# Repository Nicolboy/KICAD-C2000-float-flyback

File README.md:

# KICAD-C2000-float-flyback

- **18.9W** — real-world target power, simulated efficiency up to 92.1%
- **+4.6 to +10.7 points** efficiency from synchronous rectification (UCC24612) vs. body-diode, depending on operating point
- **107.2V → 58.4–63.5V** — secondary overvoltage, resolved by a TVS clamp sized through simulation (×1.6 margin vs. the 100V MOSFET rating)
- PCB **routed 100% on 4 layers**, DRC clean

Flyback power supply for vacuum-tube filament heating and a low-noise
preamp stage, designed in KiCad 10, with the control side (C2000)
galvanically isolated from the power stage. **Update 2026-10-25**: the
secondary is no longer floating/galvanically isolated from the primary
in the final assembly — only the control↔power barrier remains isolated;
see `doc/plan-isolation-4couches.md` for the current barrier scope.
200kHz, 11–25V in → 5.5–13V/3A out, secondary liftable 0–90V for
cathode/filament stress reduction. Synchronous secondary rectification
(UCC24612, direct Vds sensing — no firmware timing) validated by SPICE at
the real 18.9W target, including a secondary-side overvoltage finding and
the clamp that fixes it — see *Validation* below for the figures and
`doc/sim-vs-mesure.md` for the full data.

Alimentation flyback pour le chauffage de filaments de chauffage de tubes à vide, conçue sous KiCad 10 — le côté
contrôle (C2000) reste isolé galvaniquement de l'étage de puissance.
**Mise à jour 2026-10-25** : le secondaire n'est plus flottant/isolé
galvaniquement du primaire dans le montage final — seule la barrière
contrôle↔puissance reste isolée ; voir `doc/plan-isolation-4couches.md`
pour le périmètre actuel des barrières.

Convertisseur flyback 200kHz, 11-25V en entrée → 5,5-13V/3A en sortie.
Secondaire élevable de 0 à 90V par un pont symétrique 2×100kΩ (une
résistance vers Vout+, une vers Vout-) — pour réduire le stress 
cathode/chauffage et le bruit de fond sur un préamplificateur à tubes bas bruit (montage cascode).

---

## Le point de conception le plus notable

Le redressement synchrone secondaire (Q2) est piloté par un **UCC24612**, pas
par le C2000 : ce contrôleur détecte directement le Vds de Q2 (diode
emulation) et pilote sa grille tout seul — aucun signal PWM ni isolateur
dédié à faire traverser la barrière pour ce canal. Avant ça, la commande
passait par un ISO7710+UCC27517 secondaires pilotés en PWM depuis le C2000 :
un timing fixé par le firmware, « à l'aveugle », sans retour sur le vrai Vds
de Q2 — remplacé une fois ce défaut identifié. L'UCC24612 est alimenté
directement depuis Vout (VDD dans sa plage 4,5-28V, pas de bootstrap
nécessaire) ; côté primaire, l'isolation PWM/EN (ISO7710 + UCC27517 + DPC817)
reste inchangée.

Chaque composant de puissance (MOSFETs, clamp, condensateurs d'entrée et de
sortie) est sourcé avec sa propre fiche datasheet dans `composants-datasheets/data/carte-flyback/`
(dépôt interne, non public — pas de lien)
— page citée, base (absolue / recommandée / typique / calculée), jamais de
valeur choisie à l'oeil. Ce sourcing a d'ailleurs fait revenir deux fois sur
le choix de Cin et Cout : le premier calcul prenait le cas 13V/3A (39W)
comme pire cas, avant d'être recorrigé sur les vrais cas d'usage — deux
câblages de filament qui tombent à **la même puissance réelle** (18,9W) et
divisent par deux la contrainte de courant et d'ondulation retenue au départ.
Le détail (formules, marges, historique des choix) est dans
[`00-intention-conception.md`](00-intention-conception.md).

---

## Architecture

| Bloc | Rôle |
|---|---|
| Primaire | Cin, Q1 (MOSFET N TO-252), clamp TVS D1 (boîtier SMC), U1 (UCC27517) + U3 (ISO7710, PWM) |
| Isolation — commande | U3 (ISO7710, PWM primaire) + U5 (DPC817, EN) + U10 (ISO7710, PWM de polarisation HV_BIAS) — plus de canal PWM dédié au secondaire |
| Isolation — retours mesure vers C2000 | U7 (AMC0311R, `Vht`/Vout), U9 + U22 (AMC0302R, `I_Shunt_ht`/`I_Shunt_ht_comp`, voie directe + voie comparateur), U11 (AMC0311R, `V_bias`) — famille ratiométrique, isolée |
| Secondaire (non isolé du primaire depuis 2026-10-25) | Q2 (MOSFET N potentiel bas, rectification synchrone), U12 (UCC24612, détection Vds, alimenté direct depuis Vout) + clamp TVS D4 (SMCJ54A), banc Cout, pont bias 2×100kΩ |
| Polarisation (`polarisation.kicad_sch`, §16) | `HV_BIAS` piloté activement 0-78V depuis une source 80V externe dédiée (`J1`) : source de courant régulée (Q3/Q4/R25/R26), protection TVS D3, résistance variable Q5 pilotée en PWM isolé (U10), boucle de linéarisation U21 (MCP6001) + Q6/Q7 |
| Couplage | Coilcraft MSD1514-103ME, 1:1 (k=0,9798, fuite 0,40µH typ. datasheet), 10µH par enroulement |
| Limitation de courant (§19) | U14 (TSV791, ×10,09) + U16 (LMV7219, comparateur) + U17/U18 (SN74LVC1G132/74, blanking/verrou) + U13 (SN74LVC1G08, porte ET) + U19 (ISO7710F), 100% primaire sauf le retour isolé `I_Shunt_ht_comp` — coupe Q1 en ~100ns sur défaut, indépendant du C2000 |
| Connecteur C2000 | `J2` (`COM_HT`, IDC 2×10), aligné broche à broche sur `J21` du shield — remplace les anciens `CpuOut1`/`CpuIn1` (§18) |

L'isolation fonctionnelle (barrière contrôle↔puissance, via les AMC03xx/
ISO7710/DPC817) est dimensionnée pour l'écart réel présent sur la carte,
pas pour la tenue diélectrique complète des isolateurs (5000V) — pas de
slot d'isolation dans le PCB. Le primaire et le secondaire de puissance,
eux, ne sont plus traités comme deux domaines isolés (2026-10-25) : voir
`doc/plan-isolation-4couches.md`.

---

## Le schéma est généré, les feuilles sont ensuite routées à la main

```
00-intention-conception.md      source de vérité (calculs, marges, sourcing)
        │
        ├── gen_symboles.py        → lib/custom_parts.kicad_sym
        │                            (UCC27517, ISO7710, MSD1514, MOSFET 3 broches)
        │
        └── gen_composants.py      → alim.kicad_sch / flyback.kicad_sch /
              ▲                       isolation.kicad_sch (feuilles hiérarchiques)
              │                       kicad_gen.py — primitives communes
        étiquettes globales uniquement, aucun fil posé par script
```

Une fois qu'une feuille a été reprise à la main dans KiCad (repositionnement
des composants, rotation, déplacement des étiquettes Référence/Valeur), elle
devient un **fichier de travail permanent** : les générateurs ne sont plus
rejoués dessus.

ERC sur la hiérarchie complète des 6 feuilles (`alim`, `flyback`,
`isolation`, `limitation-courant`, `polarisation` + racine) : 0 erreur
(label `nQ_TRIP` sur `isolation.kicad_sch` corrigé en `~{Q_TRIP}`, deux
conventions de nom différentes pour le même signal faisaient deux nets
séparés — `U13` broche B était orpheline).
Empreintes custom
(`lib_fp/*.pretty/`) pour l'inductance couplée MSD1514, le MOSFET TO-252 et le
condensateur KEMET A786MW (V-chip), toutes construites à partir des cotes
mécaniques des datasheets plutôt que d'une empreinte générique approximative.

Placement et routage du PCB faits à la main, comme pour les autres cartes de
ce workspace. **Routé à 100 % (2026-10-29)**, DRC à 0 violation (voir
§29 de [`00-intention-conception.md`](00-intention-conception.md)) — reste
la revue de placement/routage finale et l'envoi en fabrication.

---

## Validation — simulation et mesure

| Étape                       | État                                   |
| --------------------------- | --------------------------------------- |
| Calcul analytique           | fait — [`00-intention-conception.md`](00-intention-conception.md) |
| Simulation LTspice (diode, 10W)       | étapes 1-4 faites, modèles réels (MOSFET Infineon, clamp D1) |
| Simulation LTspice (18,9W, synchrone) | faite — proxy UCC24612, clamp secondaire dimensionné |
| Redressement synchrone (KiCad)        | implémenté — UCC24612 (U12) + clamp D4 |
| Placement + routage PCB     | fait (DRC : 0 violation, 2026-10-29)   |
| Prototype                   | à fabriquer                            |
| Mesures au banc             | à faire                                |

Balayage à Vin=11/20/25V, 6V et 12V à 10W (+ un point à charge légère) :
rendement 84-91%, et la tension drain de Q2 dépasse déjà 100V (sa tenue
en tension) à Vin≥23V environ, sans clamp secondaire modélisé à ce
stade.

Autre résultat notable : la plupart des points réels fonctionnent en
**CCM**, pas en DCM comme une estimation rapide l'avait d'abord suggéré —
déterminé sur la forme d'onde (passage par zéro de I(L2)), pas supposé.
Comparé à un modèle Schottky générique simplifié (rapide mais pas le
composant réel) pour chiffrer la perte dans le clamp D1 :

Rejoué à la cible réelle (**18,9W**) avec un proxy de redressement
synchrone : le dépassement empire (dès Vin=20V au point 12,6V ; les deux
points dépassent à partir de 25V, jusqu'à 107,2V) — indépendant du
redresseur, c'est une résonance de l'inductance de fuite. Le passage en
synchrone (UCC24612) apporte +4,6 à +10,7 points de rendement selon le
point, mais ne corrige pas la surtension :

D'où le clamp secondaire **D4 (SMCJ54A)**, qui ramène Vds_Q2 à 58,4-63,5V
(marge ×1,6) pour 0-0,76W de dissipation (marge ×6,6 vs les 5W du
composant) — comparé au SMCJ43A (même réf. que D1, déjà au BOM) qui tient
aussi mais coûte jusqu'à 3,5 points de rendement de plus au pire point :

Le détail, le protocole de mesure et le tableau calcul / simulation /
mesure : [`doc/sim-vs-mesure.md`](doc/sim-vs-mesure.md) (§7/§7bis pour le
passage 18,9W) ; l'implémentation KiCad correspondante :
[`00-intention-conception.md`](00-intention-conception.md) §16.

### Linéarisation HV_BIAS (`polarisation.kicad_sch`)

La boucle qui linéarise la polarisation flottante du secondaire (MCP6001 +
Q6/Q7, contre-réaction sur HV_BIAS) a d'abord été validée avec des modèles
idéaux, puis rejouée avec les composants réels (MMBF170, MCP6001 paramétré
depuis sa datasheet) une fois le schéma modifié. Ce passage aux modèles
réels a révélé un défaut invisible sur le schéma seul : à consigne figée,
la boucle part en oscillation auto-entretenue — un cycle limite qui
grandit puis se stabilise en amplitude constante, pas du bruit de
simulation, confirmé en figeant `VAR_GATE` et en observant le régime sur
plusieurs millisecondes :

La simulation a aussi servi à trouver un premier correctif et à le vérifier
avant de toucher au vrai schéma : une résistance de dégénérescence sur la
source de Q6 (330Ω) supprime l'oscillation sans sacrifier l'accès à
`HV_BIAS`=0V, et un condensateur de compensation autour de l'ampli-op
(1nF, sortie → entrée inverseuse) élimine le dépassement en échelon, même
au pire cas (front de commande 10ns).

Ce correctif n'a été validé qu'avec un signal d'entrée déjà filtré
(échelon analogique propre) — pas avec le vrai PWM du C2000. En rejouant
la boucle avec le PWM réel, il a fallu élargir le filtre d'entrée
(1kΩ/1nF → 100kΩ/100nF) pour écraser l'ondulation résiduelle avant
l'ampli-op, ce qui a réintroduit une oscillation auto-entretenue
différente — ~700kHz cette fois, confirmée indépendante du PWM par un
échelon direct avant le filtre (l'oscillation persiste à l'identique sans
aucun PWM : c'est la boucle elle-même qui devient instable avec ce
nouveau filtre, pas une fuite du signal de commande). Le premier
correctif n'avait jamais été vérifié pour ce filtre élargi.

Reporté : résistance de dégénérescence à 1kΩ (au lieu de 330Ω) et
condensateur de compensation à 100pF (au lieu de 1nF) stabilisent la
boucle avec le nouveau filtre d'entrée — vérifié sur le profil complet de
commande PWM (rapport cyclique 1%→60%→palier→99%→palier→40%→1%, 3,5s),
ondulation résiduelle en sortie sous le mV grâce au filtre de sortie déjà
en place :

---

## Licence

CERN-OHL-S v2 — voir [`LICENSE`](LICENSE).

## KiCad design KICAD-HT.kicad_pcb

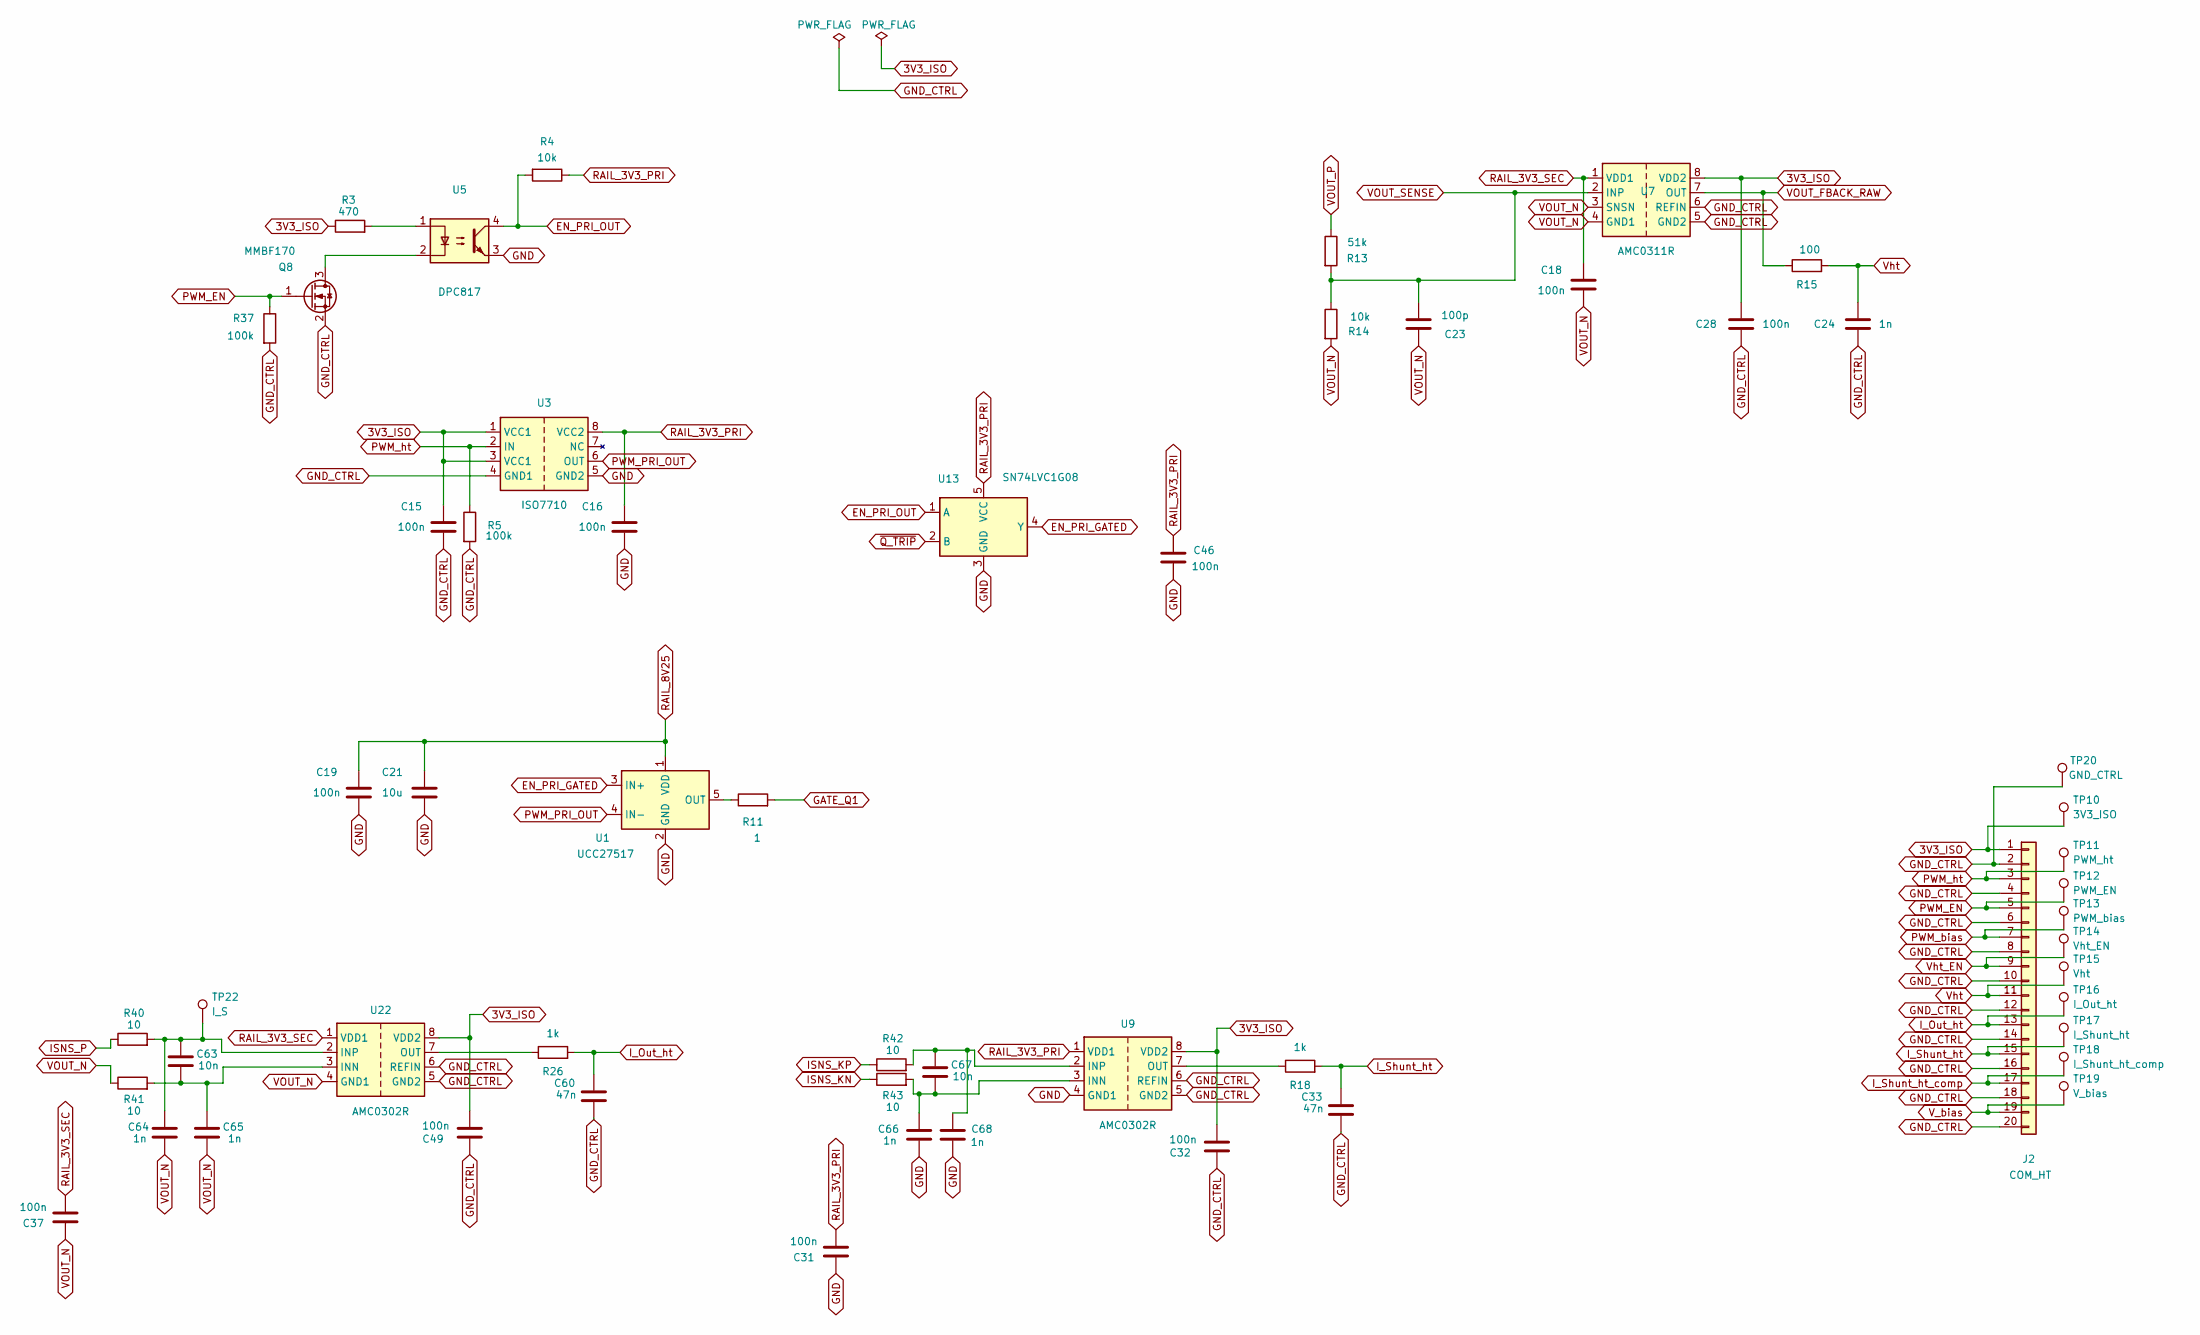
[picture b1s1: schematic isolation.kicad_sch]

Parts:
C15, C16, C18, C19, C28, C31, C32, C37, C46, C49: 100n; C_0805_2012Metric
C21: 10u; C_0805_2012Metric
C23: 100p; C_0805_2012Metric
C24, C64, C65, C66, C68: 1n; C_0805_2012Metric
C33, C60: 47n; C_0805_2012Metric
C63, C67: 10n; C_0805_2012Metric
J2: COM_HT; IDC-Header_2x10_P2.54mm_Vertical
Q8: MMBF170; SOT-23
R3: 470; R_0805_2012Metric
R4, R14: 10k; R_0805_2012Metric
R5, R37: 100k; R_0805_2012Metric
R11: 1; R_0805_2012Metric
R13: 51k; R_0805_2012Metric
R15: 100; R_0805_2012Metric
R18, R26: 1k; R_0805_2012Metric
R40, R41, R42, R43: 10; R_0805_2012Metric
TP10: 3V3_ISO; TestPoint_Pad_D1.5mm
TP11: PWM_ht; TestPoint_Pad_D1.5mm
TP12: PWM_EN; TestPoint_Pad_D1.5mm
TP13: PWM_bias; TestPoint_Pad_D1.5mm
TP14: Vht_EN; TestPoint_Pad_D1.5mm
TP15: Vht; TestPoint_Pad_D1.5mm
TP16: I_Out_ht; TestPoint_Pad_D1.5mm
TP17: I_Shunt_ht; TestPoint_Pad_D1.5mm
TP18: I_Shunt_ht_comp; TestPoint_Pad_D1.5mm
TP19: V_bias; TestPoint_Pad_D1.5mm
TP20: GND_CTRL; PinHeader_1x01_P2.54mm_Vertical
TP22: I_S; TestPoint_Pad_D1.5mm
U1: UCC27517; SOT-23-5
U3: ISO7710; SOIC-8_3.9x4.9mm_P1.27mm
U5: DPC817; SMDIP-4_W7.62mm
U7: AMC0311R; SOIC-8_DWV_5.85x11.5mm_P1.27mm
U9, U22: AMC0302R; SOIC-8_DWV_5.85x11.5mm_P1.27mm
U13: SN74LVC1G08; SOT-23-5

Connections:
3V3_ISO: C15.1, C28.1, C32.1, C49.1, J2.1, R3.1, TP10.1 (1_1), U3.1 (VCC1), U3.3 (VCC1), U7.8 (VDD2), U9.8 (VDD2), U22.8 (VDD2); also elsewhere on the board
EN_PRI_GATED: U1.3 (IN+), U13.4 (Y)
EN_PRI_OUT: R4.2, U5.4, U13.1 (A)
GATE_Q1: R11.2; also elsewhere on the board
GND: C16.2, C19.2, C21.2, C31.2, C46.2, C66.2, C68.2, U1.2 (GND), U3.5 (GND2), U5.3, U9.4 (GND1), U13.3 (GND); also elsewhere on the board
GND_CTRL: C15.2, C24.2, C28.2, C32.2, C33.2, C49.2, C60.2, J2.2, J2.4, J2.6, J2.8, J2.10, J2.12, J2.14, J2.16, J2.18, J2.20, Q8.2 (S), R5.2, R37.2, TP20.1 (1_1), U3.4 (GND1), U7.5 (GND2), U7.6 (REFIN), U9.5 (GND2), U9.6 (REFIN), U22.5 (GND2), U22.6 (REFIN); also elsewhere on the board
ISNS_KN: R43.1; also elsewhere on the board
ISNS_KP: R42.1; also elsewhere on the board
ISNS_P: R40.1; also elsewhere on the board
I_Out_ht: C60.1, J2.13, R26.2, TP16.1 (1_1)
I_Shunt_ht: C33.1, J2.15, R18.2, TP17.1 (1_1)
I_Shunt_ht_comp: J2.17, TP18.1 (1_1); also elsewhere on the board
unnamed: Q8.3 (D), U5.2
unnamed: R3.2, U5.1
unnamed: R11.1, U1.5 (OUT)
unnamed: C66.1, C67.2, R43.2, U9.3 (INN)
unnamed: C67.1, C68.1, R42.2, U9.2 (INP)
unnamed: R18.1, U9.7 (OUT)
unnamed: C63.2, C65.1, R41.2, U22.3 (INN)
unnamed: C63.1, C64.1, R40.2, TP22.1 (1_1), U22.2 (INP)
unnamed: R26.1, U22.7 (OUT)
PWM_EN: J2.5, Q8.1 (G), R37.1, TP12.1 (1_1)
PWM_PRI_OUT: U1.4 (IN-), U3.6 (OUT); also elsewhere on the board
PWM_bias: J2.7, TP13.1 (1_1); also elsewhere on the board
PWM_ht: J2.3, R5.1, TP11.1 (1_1), U3.2 (IN)
RAIL_3V3_PRI: C16.1, C31.1, C46.1, R4.1, U3.8 (VCC2), U9.1 (VDD1), U13.5 (VCC); also elsewhere on the board
RAIL_3V3_SEC: C18.1, C37.1, U7.1 (VDD1), U22.1 (VDD1); also elsewhere on the board
RAIL_8V25: C19.1, C21.1, U1.1 (VDD); also elsewhere on the board
VOUT_FBACK_RAW: R15.1, U7.7 (OUT)
VOUT_N: C18.2, C23.2, C37.2, C64.2, C65.2, R14.2, R41.1, U7.3 (SNSN), U7.4 (GND1), U22.4 (GND1); also elsewhere on the board
VOUT_P: R13.1; also elsewhere on the board
VOUT_SENSE: C23.1, R13.2, R14.1, U7.2 (INP)
V_bias: J2.19, TP19.1 (1_1); also elsewhere on the board
Vht: C24.1, J2.11, R15.2, TP15.1 (1_1)
Vht_EN: J2.9, TP14.1 (1_1); also elsewhere on the board
~Q_TRIP: U13.2 (B); also elsewhere on the board

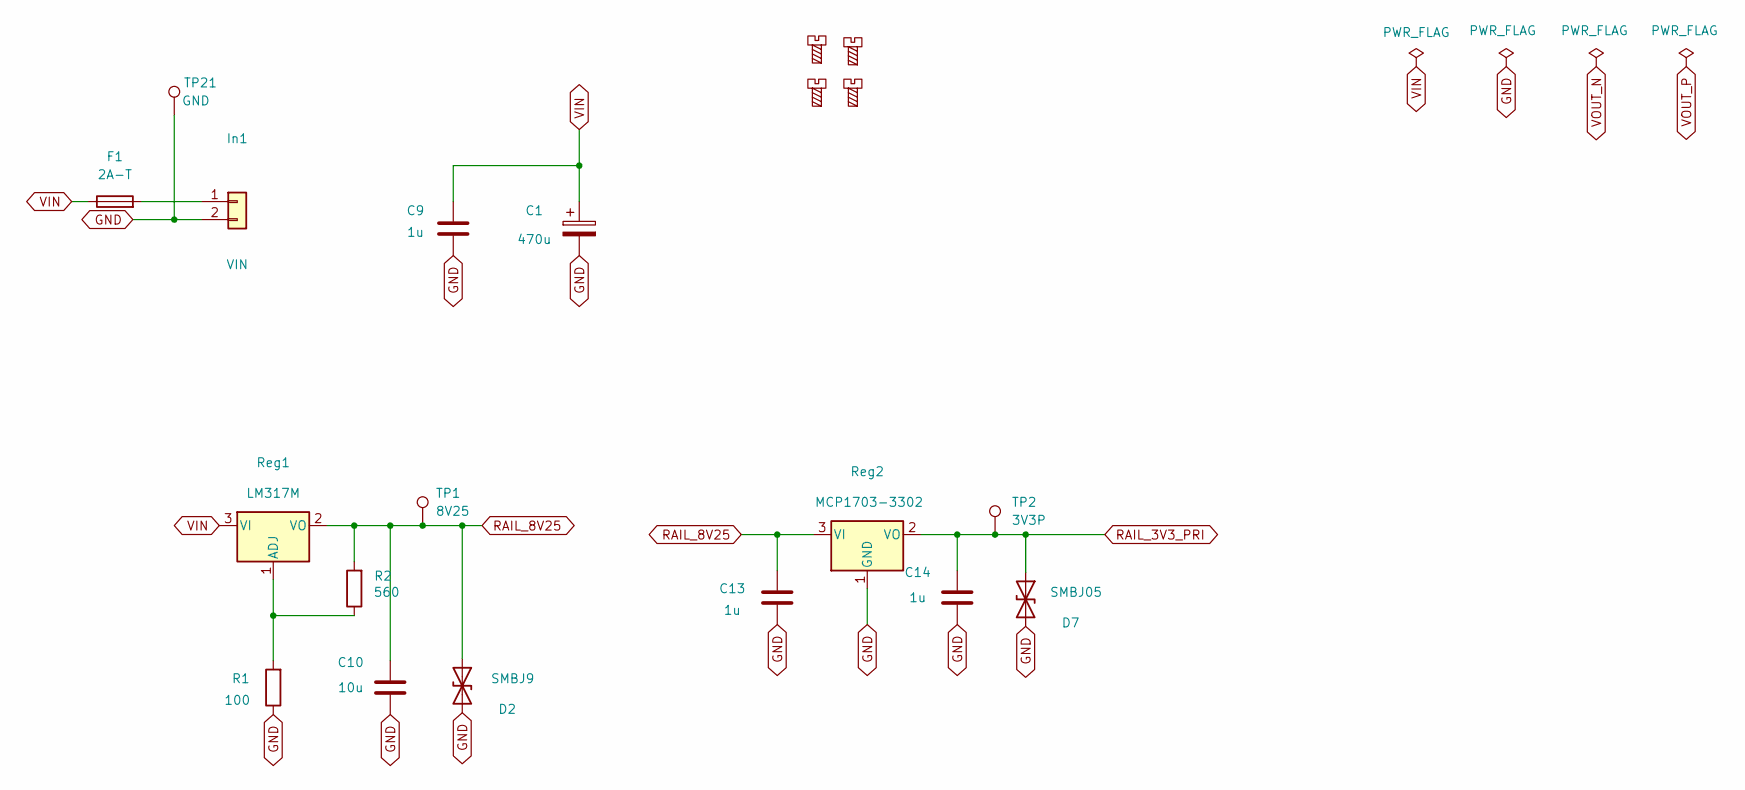
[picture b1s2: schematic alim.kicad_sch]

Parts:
C1: 470u; A786MW_VChip
C9, C13, C14: 1u; C_0805_2012Metric
C10: 10u; C_0805_2012Metric
D2: SMBJ9; D_SMB
D7: SMBJ05; D_SMB
F1: 2A-T; Fuseholder_Clip-5x20mm_Littelfuse_111_Lateral_P18.80x5.00mm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
H1, H2, H3, H4: MountingScrew; MountingHole_3.2mm_M3
In1: VIN; PinHeader_1x02_P2.54mm_Vertical
R1: 100; R_0805_2012Metric
R2: 560; R_0805_2012Metric
Reg1: LM317M; SOT-223-3_TabPin2
Reg2: MCP1703-3302; SOT-23-3
TP1: 8V25; TestPoint_Pad_D1.5mm
TP2: 3V3P; TestPoint_Pad_D1.5mm
TP21: GND; PinHeader_1x01_P2.54mm_Vertical

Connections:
GND: C1.2, C9.2, C10.2, C13.2, C14.2, D2.2 (A2), D7.2 (A2), In1.2, R1.1, Reg2.1 (GND), TP21.1 (1_1); also elsewhere on the board
unnamed: F1.2, In1.1
unnamed: R1.2, R2.1, Reg1.1 (ADJ)
RAIL_3V3_PRI: C14.1, D7.1 (A1), Reg2.2 (VO), TP2.1 (1_1); also elsewhere on the board
RAIL_8V25: C10.1, C13.1, D2.1 (A1), R2.2, Reg1.2 (VO), Reg2.3 (VI), TP1.1 (1_1); also elsewhere on the board
VIN: C1.1, C9.1, F1.1, Reg1.3 (VI); also elsewhere on the board

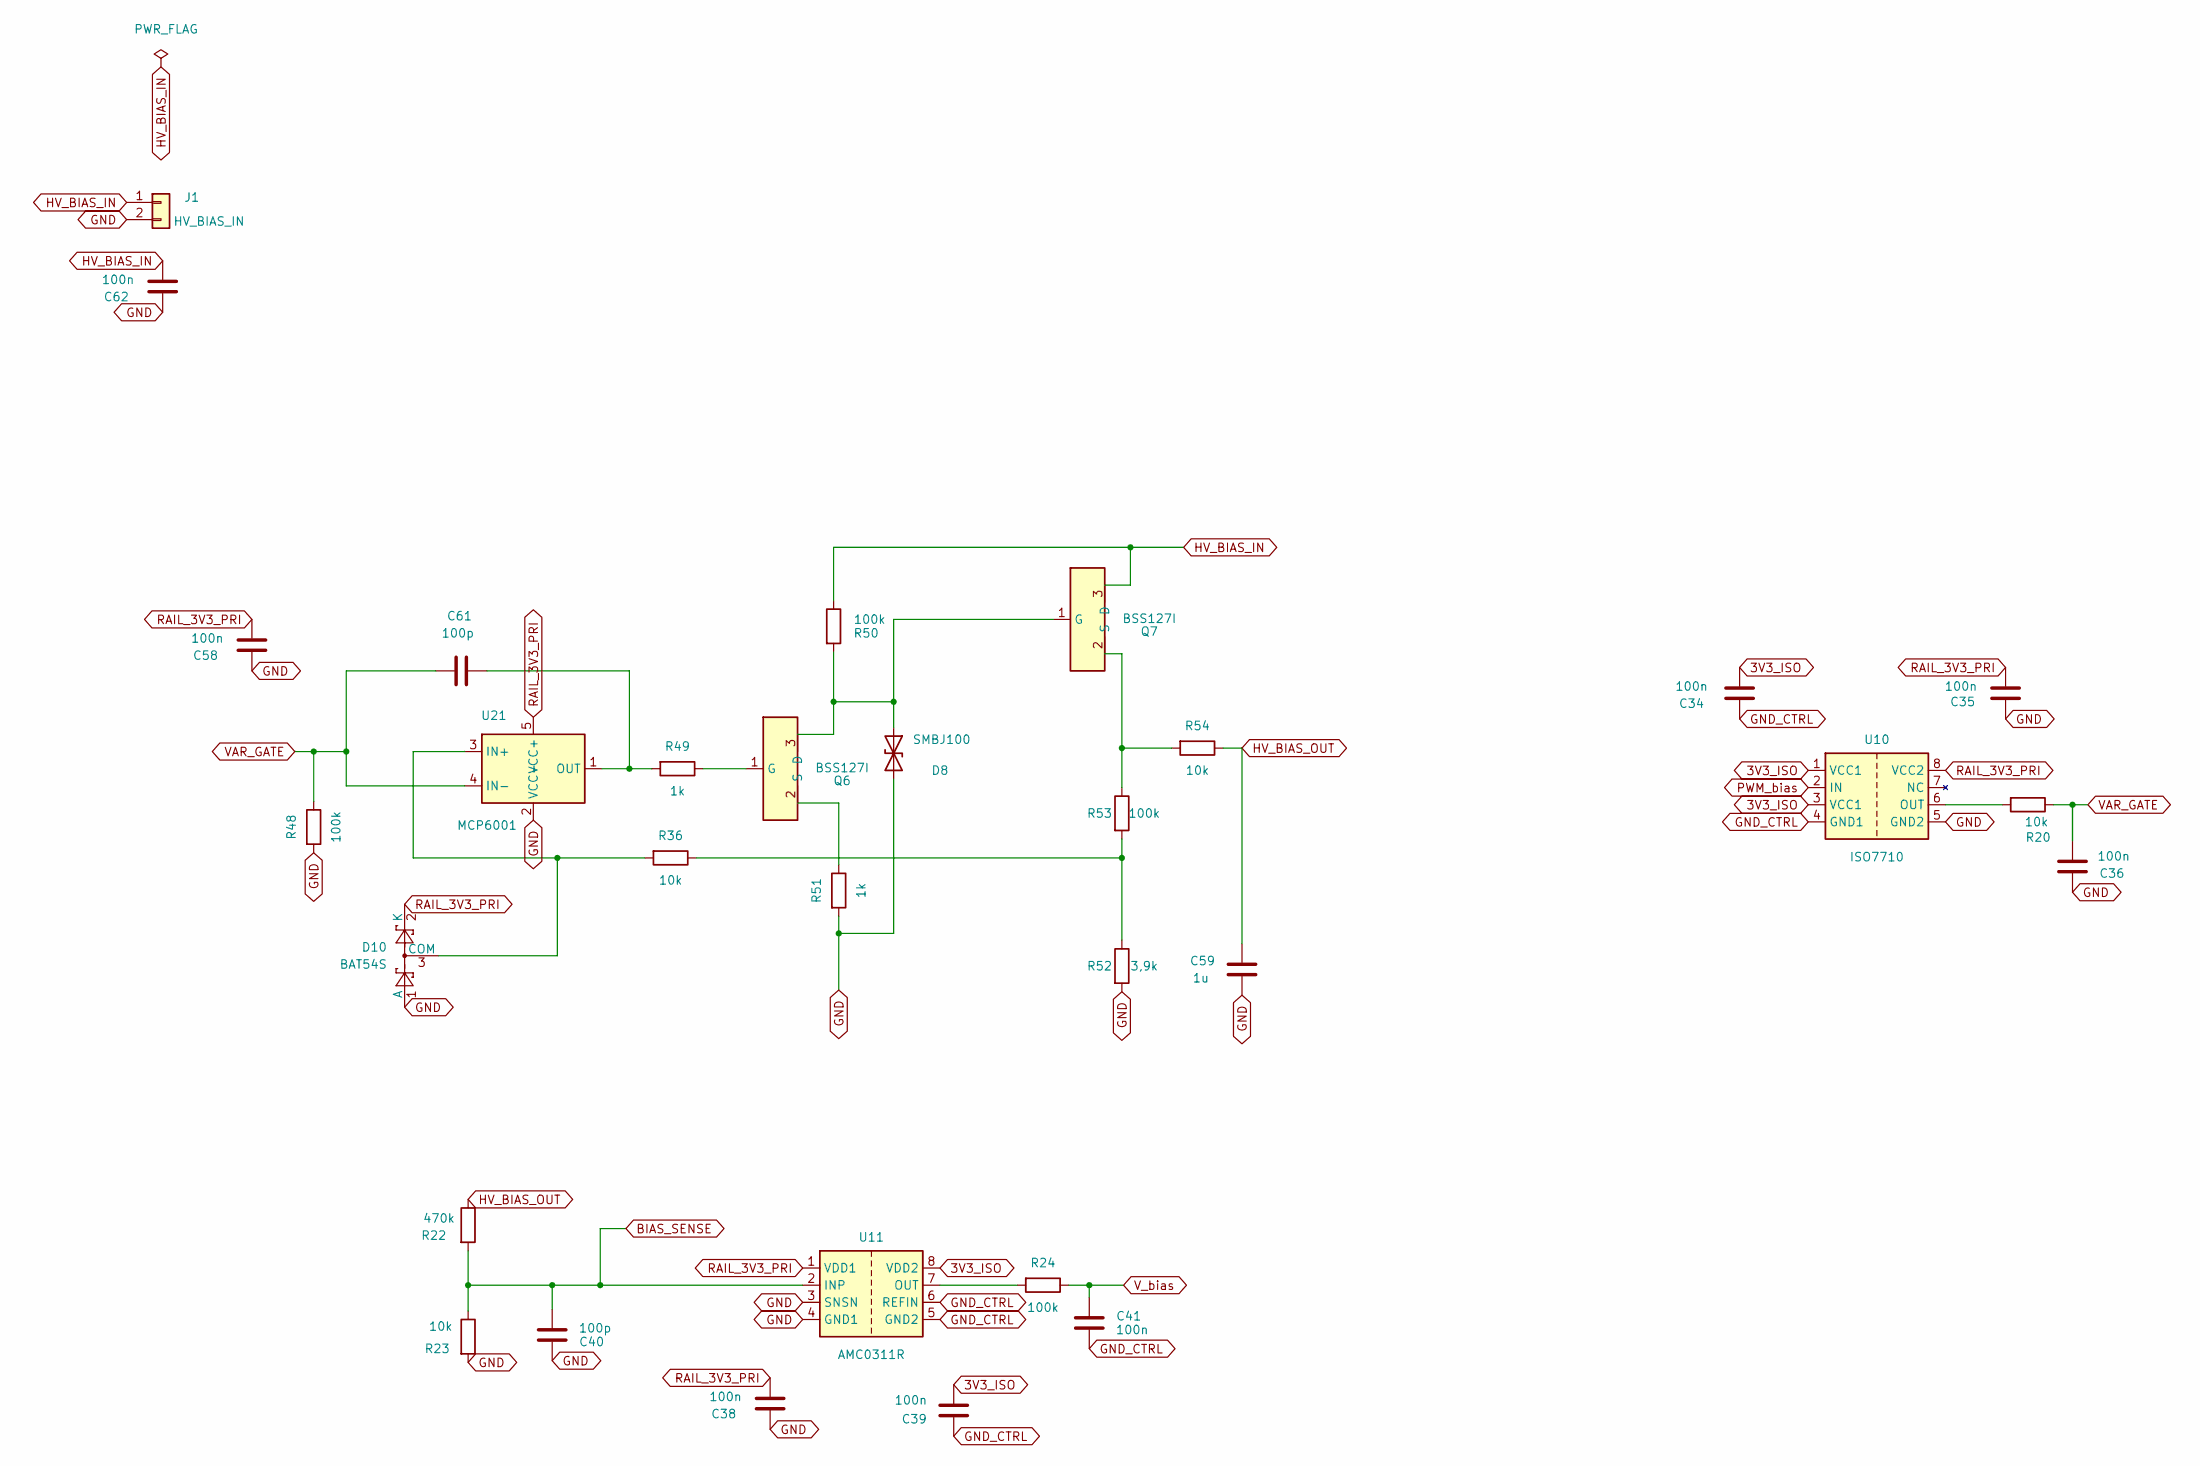
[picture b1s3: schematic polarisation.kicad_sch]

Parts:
C34, C35, C36, C38, C39, C41, C58, C62: 100n; C_0805_2012Metric
C40, C61: 100p; C_0805_2012Metric
C59: 1u; C_0805_2012Metric
D8: SMBJ100; D_SMB
D10: BAT54S; SOT-23
J1: HV_BIAS_IN; PinHeader_1x02_P2.54mm_Vertical
Q6, Q7: BSS127I; SOT-23
R20, R23, R36, R54: 10k; R_0805_2012Metric
R22: 470k; R_0805_2012Metric
R24, R48, R50, R53: 100k; R_0805_2012Metric
R49, R51: 1k; R_0805_2012Metric
R52: 3,9k; R_0805_2012Metric
U10: ISO7710; SOIC-8_3.9x4.9mm_P1.27mm
U11: AMC0311R; SOIC-8_DWV_5.85x11.5mm_P1.27mm
U21: MCP6001; SOT-23-5

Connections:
3V3_ISO: C34.1, C39.1, U10.1 (VCC1), U10.3 (VCC1), U11.8 (VDD2); also elsewhere on the board
BIAS_SENSE: C40.1, R22.2, R23.1, U11.2 (INP)
GND: C35.2, C36.2, C38.2, C40.2, C58.2, C59.2, C62.2, D8.2 (A2), D10.1 (A), J1.2, R23.2, R48.2, R51.2, R52.2, U10.5 (GND2), U11.3 (SNSN), U11.4 (GND1), U21.2 (VCC-); also elsewhere on the board
GND_CTRL: C34.2, C39.2, C41.2, U10.4 (GND1), U11.5 (GND2), U11.6 (REFIN); also elsewhere on the board
HV_BIAS_IN: C62.1, J1.1, Q7.3 (D), R50.1
HV_BIAS_OUT: C59.1, R22.1, R54.1; also elsewhere on the board
unnamed: D8.1 (A1), Q6.3 (D), Q7.1 (G), R50.2
unnamed: D10.3 (COM), R36.2, U21.3 (IN+)
unnamed: Q6.1 (G), R49.1
unnamed: Q6.2 (S), R51.1
unnamed: Q7.2 (S), R53.1, R54.2
unnamed: R36.1, R52.1, R53.2
unnamed: R20.2, U10.6 (OUT)
unnamed: R24.2, U11.7 (OUT)
unnamed: C61.1, R49.2, U21.1 (OUT)
PWM_bias: U10.2 (IN); also elsewhere on the board
RAIL_3V3_PRI: C35.1, C38.1, C58.1, D10.2 (K), U10.8 (VCC2), U11.1 (VDD1), U21.5 (VCC+); also elsewhere on the board
VAR_GATE: C36.1, C61.2, R20.1, R48.1, U21.4 (IN-)
V_bias: C41.1, R24.1; also elsewhere on the board

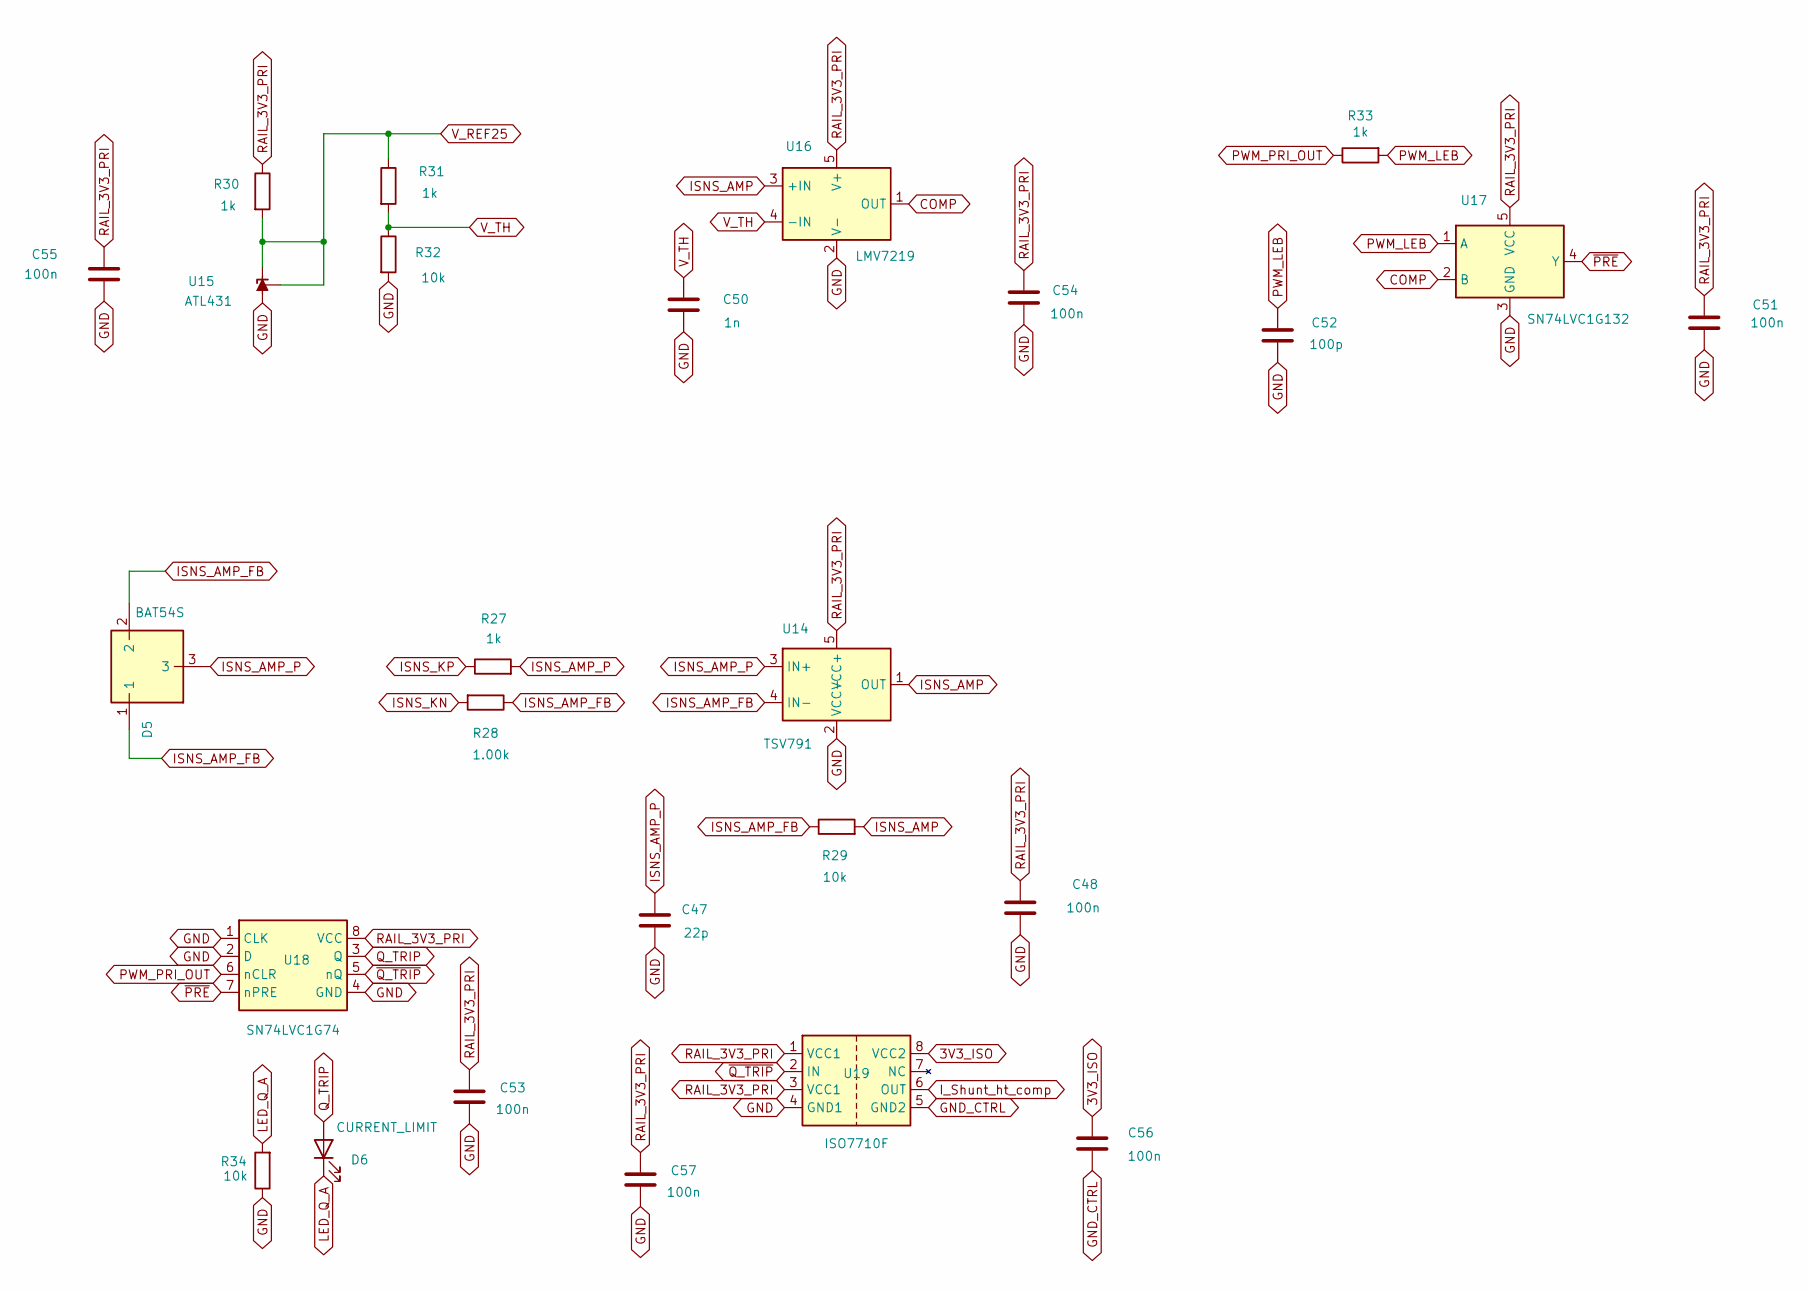
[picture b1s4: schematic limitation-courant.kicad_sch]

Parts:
C47: 22p; C_0805_2012Metric
C48, C51, C53, C54, C55, C56, C57: 100n; C_0805_2012Metric
C50: 1n; C_0805_2012Metric
C52: 100p; C_0805_2012Metric
D5: BAT54S; SOT-23
D6: CURRENT_LIMIT; LED_D3.0mm
R27, R30, R31, R33: 1k; R_0805_2012Metric
R28: 1.00k; R_0805_2012Metric
R29, R32, R34: 10k; R_0805_2012Metric
U14: TSV791; SOT-23-5
U15: ATL431; SOT-23
U16: LMV7219; SOT-23-5
U17: SN74LVC1G132; SOT-23-5
U18: SN74LVC1G74; VSSOP-8_3x3mm_P0.65mm
U19: ISO7710F; SOIC-8_3.9x4.9mm_P1.27mm

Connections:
3V3_ISO: C56.1, U19.8 (VCC2); also elsewhere on the board
COMP: U16.1 (OUT), U17.2 (B)
GND: C47.2, C48.2, C50.2, C51.2, C52.2, C53.2, C54.2, C55.2, C57.2, R32.2, R34.1, U14.2 (VCC-), U15.3 (A), U16.2 (V-), U17.3 (GND), U18.1 (CLK), U18.2 (D), U18.4 (GND), U19.4 (GND1); also elsewhere on the board
GND_CTRL: C56.2, U19.5 (GND2); also elsewhere on the board
ISNS_AMP: R29.2, U14.1 (OUT), U16.3 (+IN)
ISNS_AMP_FB: D5.1, D5.2, R28.1, R29.1, U14.4 (IN-)
ISNS_AMP_P: C47.1, D5.3, R27.2, U14.3 (IN+)
ISNS_KN: R28.2; also elsewhere on the board
ISNS_KP: R27.1; also elsewhere on the board
I_Shunt_ht_comp: U19.6 (OUT); also elsewhere on the board
LED_Q_A: D6.1 (K), R34.2
PWM_LEB: C52.1, R33.2, U17.1 (A)
PWM_PRI_OUT: R33.1, U18.6 (nCLR); also elsewhere on the board
Q_TRIP: D6.2 (A), U18.3 (Q)
RAIL_3V3_PRI: C48.1, C51.1, C53.1, C54.1, C55.1, C57.1, R30.1, U14.5 (VCC+), U16.5 (V+), U17.5 (VCC), U18.8 (VCC), U19.1 (VCC1), U19.3 (VCC1); also elsewhere on the board
V_REF25: R30.2, R31.1, U15.1 (K), U15.2 (REF)
V_TH: C50.1, R31.2, R32.1, U16.4 (-IN)
~PRE: U17.4 (Y), U18.7 (nPRE)
~Q_TRIP: U18.5 (nQ), U19.2 (IN); also elsewhere on the board

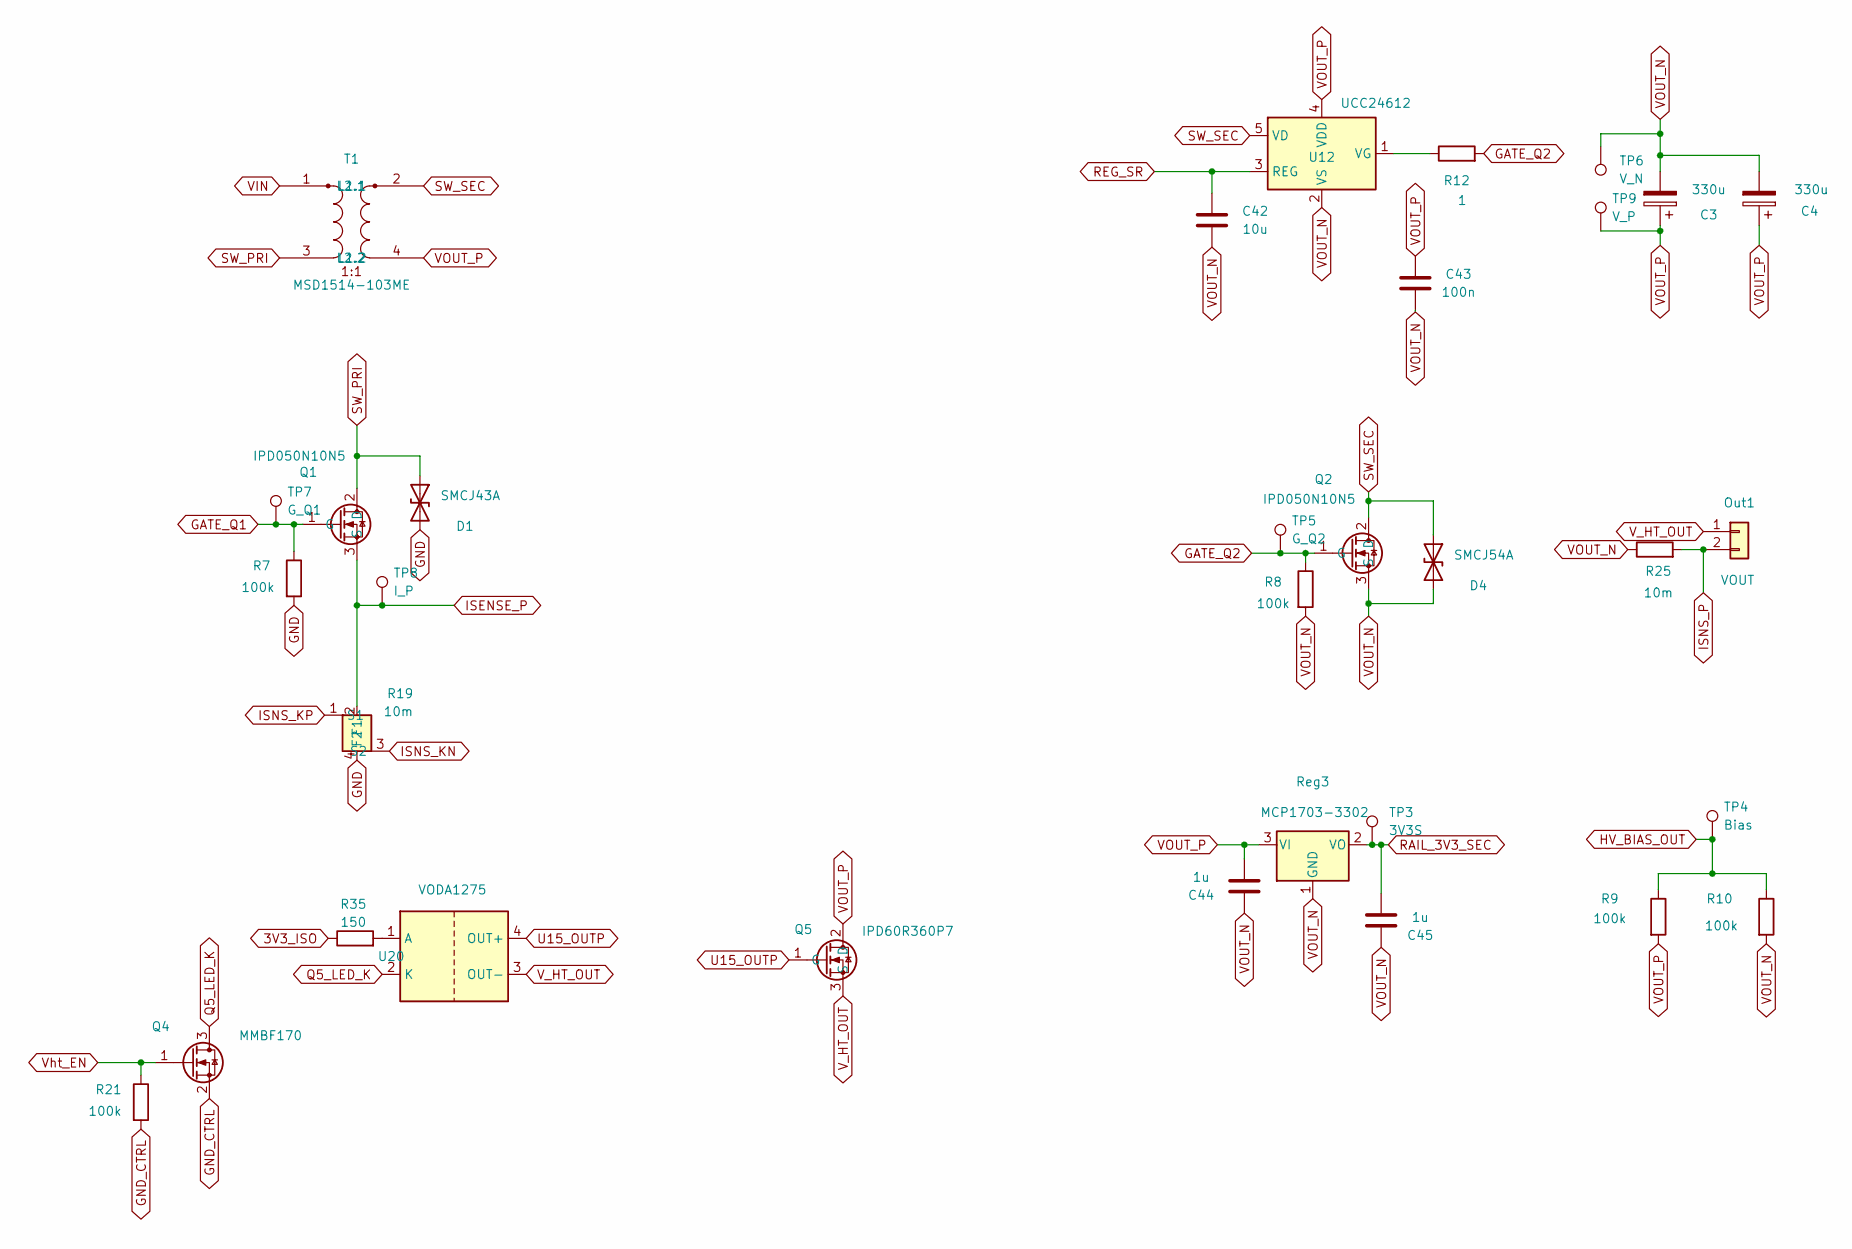
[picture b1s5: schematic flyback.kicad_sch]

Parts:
C3, C4: 330u; CP_Elec_6.3x9.9
C42: 10u; C_0805_2012Metric
C43: 100n; C_0805_2012Metric
C44, C45: 1u; C_0805_2012Metric
D1: SMCJ43A; D_SMC
D4: SMCJ54A; D_SMC
Out1: VOUT; PinHeader_1x02_P2.54mm_Vertical
Q1, Q2: IPD050N10N5; TO252-3_TabPin2
Q4: MMBF170; SOT-23
Q5: IPD60R360P7; TO252-3_TabPin2
R7, R8, R9, R10, R21: 100k; R_0805_2012Metric
R12: 1; R_0805_2012Metric
R19: 10m; WSK1206R0100FEA
R25: 10m; R_1210_3225Metric_Pad1.30x2.65mm_HandSolder
R35: 150; R_0805_2012Metric
Reg3: MCP1703-3302; SOT-23-3
T1: MSD1514-103ME; MSD1514
TP3: 3V3S; TestPoint_Pad_D1.5mm
TP4: Bias; TestPoint_Pad_D1.5mm
TP5: G_Q2; TestPoint_Pad_D1.5mm
TP6: V_N; TestPoint_Pad_D1.5mm
TP7: G_Q1; TestPoint_Pad_D1.5mm
TP8: I_P; TestPoint_Pad_D1.5mm
TP9: V_P; TestPoint_Pad_D1.5mm
U12: UCC24612; SOT-23-5
U20: VODA1275; SMD-4_VODA1275_VIS

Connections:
3V3_ISO: R35.1; also elsewhere on the board
GATE_Q1: Q1.1 (G), R7.1, TP7.1 (1_1); also elsewhere on the board
GATE_Q2: Q2.1 (G), R8.1, R12.2, TP5.1 (1_1)
GND: D1.2 (A2), R7.2, R19.4 (F2); also elsewhere on the board
GND_CTRL: Q4.2 (S), R21.2; also elsewhere on the board
HV_BIAS_OUT: R9.1, R10.1, TP4.1 (1_1); also elsewhere on the board
ISENSE_P: Q1.3 (S), R19.2 (F1), TP8.1 (1_1)
ISNS_KN: R19.3 (S2); also elsewhere on the board
ISNS_KP: R19.1 (S1); also elsewhere on the board
ISNS_P: Out1.2, R25.2; also elsewhere on the board
unnamed: R12.1, U12.1 (VG)
unnamed: R35.2, U20.1 (A)
Q5_LED_K: Q4.3 (D), U20.2 (K)
RAIL_3V3_SEC: C45.1, Reg3.2 (VO), TP3.1 (1_1); also elsewhere on the board
REG_SR: C42.2, U12.3 (REG)
SW_PRI: D1.1 (A1), Q1.2 (D), T1.3 (L1.2)
SW_SEC: D4.1 (A1), Q2.2 (D), T1.2 (L2.1), U12.5 (VD)
U15_OUTP: Q5.1 (G), U20.4 (OUT+)
VIN: T1.1 (L1.1); also elsewhere on the board
VOUT_N: C3.2, C4.2, C42.1, C43.1, C44.2, C45.2, D4.2 (A2), Q2.3 (S), R8.2, R10.2, R25.1, Reg3.1 (GND), TP6.1 (1_1), U12.2 (VS); also elsewhere on the board
VOUT_P: C3.1, C4.1, C43.2, C44.1, Q5.2 (D), R9.2, Reg3.3 (VI), T1.4 (L2.2), TP9.1 (1_1), U12.4 (VDD); also elsewhere on the board
V_HT_OUT: Out1.1, Q5.3 (S), U20.3 (OUT-)
Vht_EN: Q4.1 (G), R21.1; also elsewhere on the board
